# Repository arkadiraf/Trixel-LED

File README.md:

# Trixel-LED
Trixel LED is an interactive LED kit,
Create your own interactive Light elements by soldering basic shapes, such as triangle, square, pentagon and Hexagon. to create an interactive LED sculpture.

### [Trixel LED on Hackaday](https://hackaday.io/project/20510-trixel-led)

<br /><span xmlns:dct="http://purl.org/dc/terms/" property="dct:title">Trixel-LED</span> is licensed under a <a rel="license" href="http://creativecommons.org/licenses/by-nc-sa/4.0/">Creative Commons Attribution-NonCommercial-ShareAlike 4.0 International License</a>.

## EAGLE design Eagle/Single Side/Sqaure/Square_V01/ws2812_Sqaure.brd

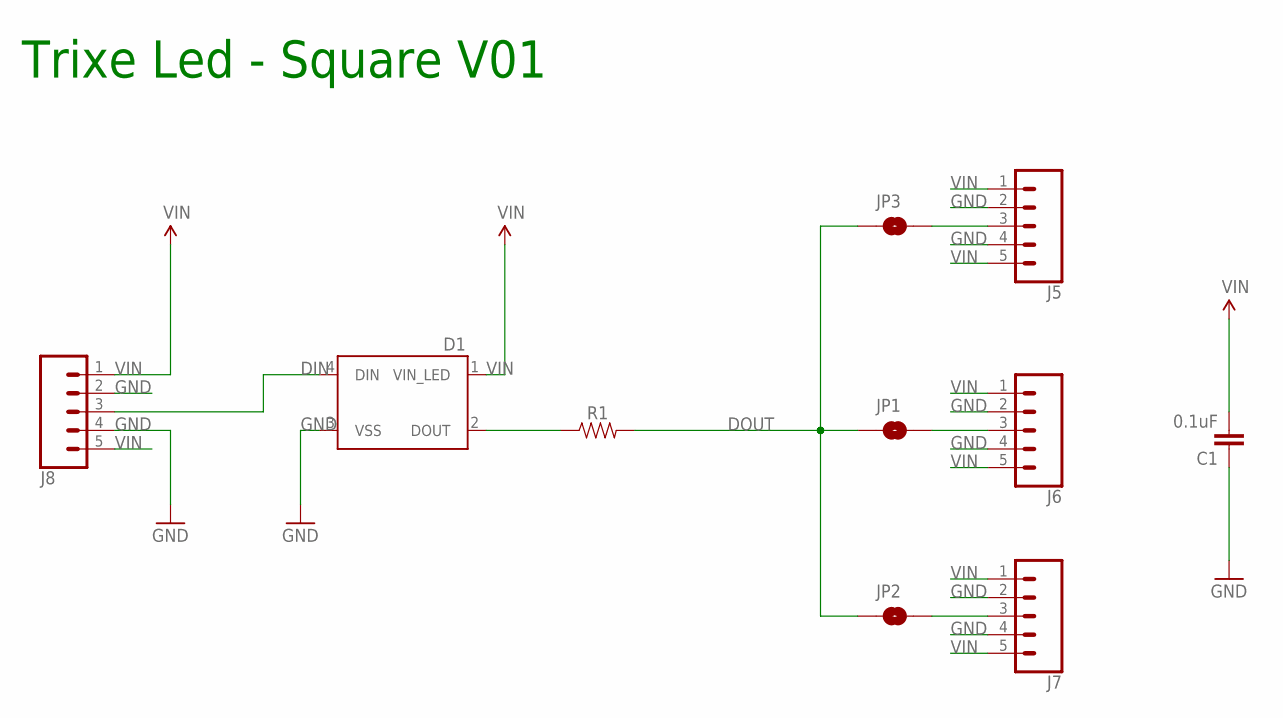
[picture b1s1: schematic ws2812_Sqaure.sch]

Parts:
C1: 0.1uF; 0805
D1: WS2812B
J5, J6, J7, J8: CONN_05PTH_LONGPADS; 1X05_LONGPADS
JP1, JP2, JP3: JUMPER-PAD-2-NOYES_SILK; PAD-JUMPER-2-NO_YES_SILK
R1: 0805

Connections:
DIN: D1.4 (DIN), J8.3
DOUT: JP1.1, JP2.1, JP3.1, R1.2
GND: C1.1, D1.3 (VSS), J5.2, J5.4, J6.2, J6.4, J7.2, J7.4, J8.2, J8.4
unnamed: J7.3, JP2.2
unnamed: J6.3, JP1.2
unnamed: J5.3, JP3.2
unnamed: D1.2 (DOUT), R1.1
VIN: C1.2, D1.1 (VIN_LED), J5.1, J5.5, J6.1, J6.5, J7.1, J7.5, J8.1, J8.5

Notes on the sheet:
Trixe Led - Square V01

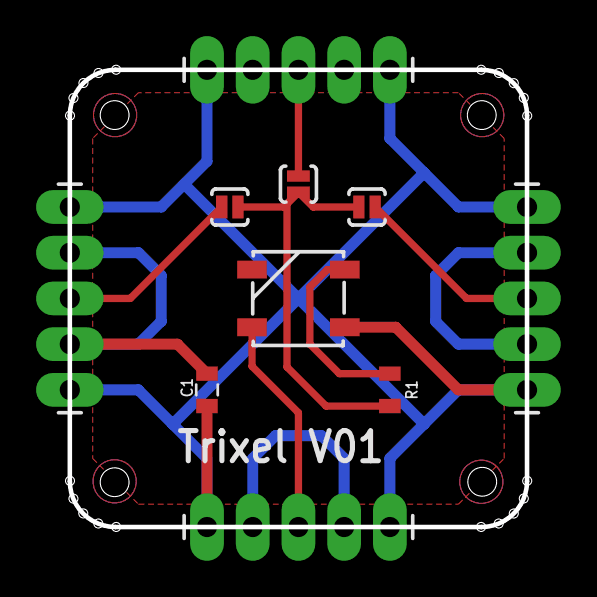
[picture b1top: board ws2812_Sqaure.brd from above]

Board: 2 copper layers, 25.4 x 25.4 mm, 10 parts (0 on the bottom side), 8 nets.

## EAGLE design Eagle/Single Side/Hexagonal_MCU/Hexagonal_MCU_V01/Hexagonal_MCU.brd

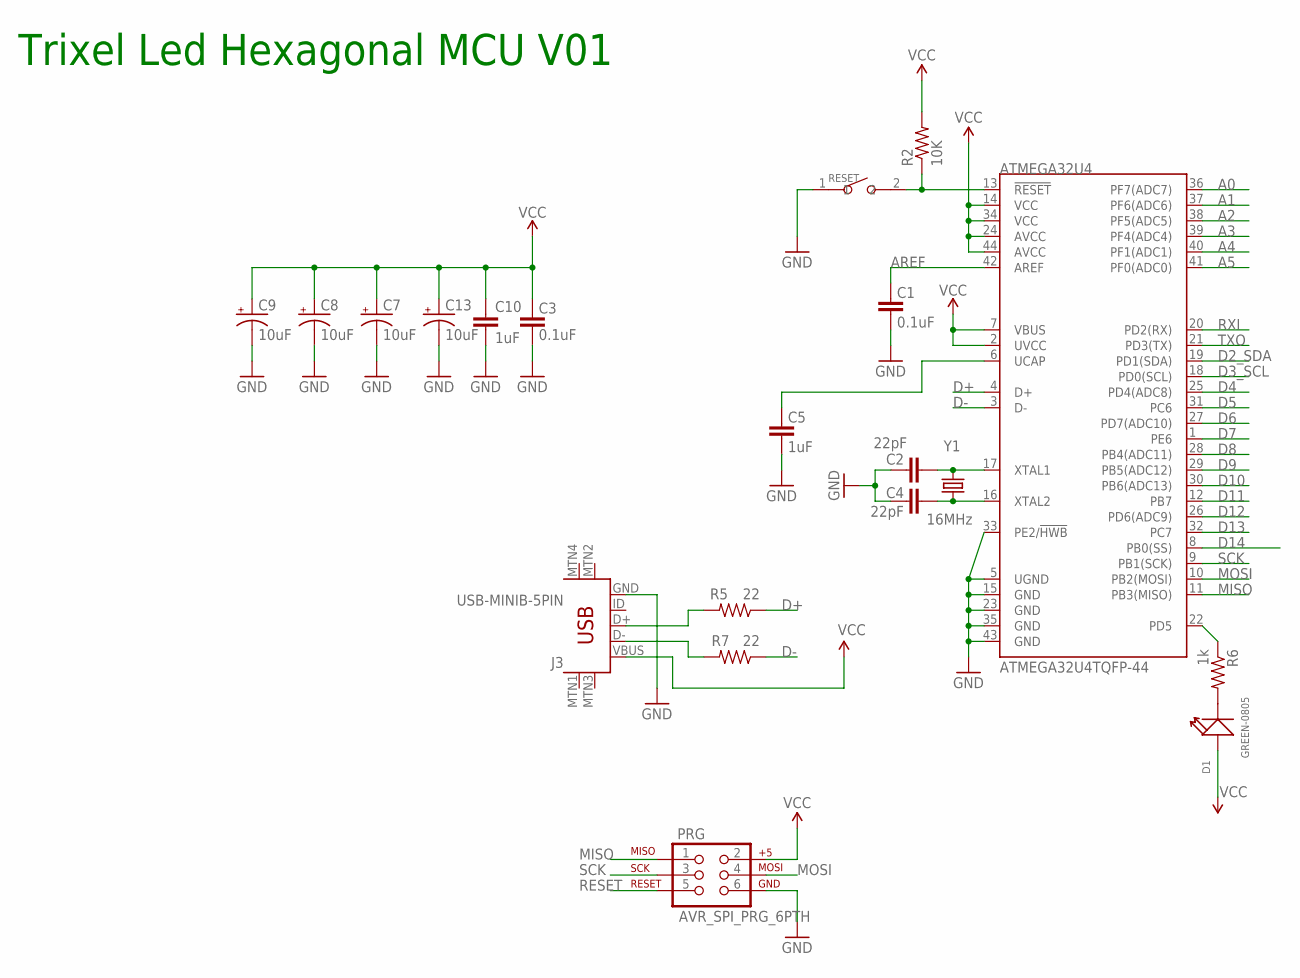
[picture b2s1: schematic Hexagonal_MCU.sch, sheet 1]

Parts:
ATMEGA32U4: ATMEGA32U4TQFP-44; TQFP44
C1, C3: 0.1uF; 0805
C2, C4: 22pF; 0805
C5, C10: 1uF; 0805
C7, C8, C9, C13: 10uF; EIA3216
D1: GREEN-0805; LED-0805
J3: USB-MINIB-5PIN; USB-MINIB
PRG: AVR_SPI_PRG_6PTH; 2X3
R2: 10K; 0805
R5, R7: 22; 0805
R6: 1k; 0805
RESET: B3U-1000P-2P-SMD; SW2-4.0X3.0X2.0
Y1: 16MHz; HC49US

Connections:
5V: ATMEGA32U4.2 (UVCC), ATMEGA32U4.7 (VBUS), ATMEGA32U4.14 (VCC), ATMEGA32U4.24 (AVCC), ATMEGA32U4.34 (VCC), ATMEGA32U4.44 (AVCC), C3.2, C7.A (+), C8.A (+), C9.A (+), C10.1, C13.A (+), D1.+, J3.VBUS, PRG.2, R2.2; also elsewhere on the board
A0: ATMEGA32U4.36 (PF7(ADC7))
A1: ATMEGA32U4.37 (PF6(ADC6))
A2: ATMEGA32U4.38 (PF5(ADC5))
A3: ATMEGA32U4.39 (PF4(ADC4))
A4: ATMEGA32U4.40 (PF1(ADC1))
A5: ATMEGA32U4.41 (PF0(ADC0))
AREF: ATMEGA32U4.42 (AREF), C1.2
D2_SDA: ATMEGA32U4.19 (PD1(SDA)); also elsewhere on the board
D3_SCL: ATMEGA32U4.18 (PD0(SCL))
D4: ATMEGA32U4.25 (PD4(ADC8))
D5: ATMEGA32U4.31 (PC6); also elsewhere on the board
D6: ATMEGA32U4.27 (PD7(ADC10))
D7: ATMEGA32U4.1 (PE6); also elsewhere on the board
D8: ATMEGA32U4.28 (PB4(ADC11)); also elsewhere on the board
D9: ATMEGA32U4.29 (PB5(ADC12))
D10: ATMEGA32U4.30 (PB6(ADC13))
D11: ATMEGA32U4.12 (PB7); also elsewhere on the board
D12: ATMEGA32U4.26 (PD6(ADC9))
D13: ATMEGA32U4.32 (PC7)
D14: ATMEGA32U4.8 (PB0(SS))
D+: ATMEGA32U4.4 (D+), R5.1
D-: ATMEGA32U4.3 (D-), R7.1
GND: ATMEGA32U4.5 (UGND), ATMEGA32U4.15 (GND), ATMEGA32U4.23 (GND), ATMEGA32U4.33 (PE2/!HWB), ATMEGA32U4.35 (GND), ATMEGA32U4.43 (GND), C1.1, C2.2, C3.1, C4.2, C5.1, C7.C (-), C8.C (-), C9.C (-), C10.2, C13.C (-), J3.GND, PRG.6, RESET.1; also elsewhere on the board
MISO: ATMEGA32U4.11 (PB3(MISO)), PRG.1
MOSI: ATMEGA32U4.10 (PB2(MOSI)), PRG.4
unnamed: ATMEGA32U4.16 (XTAL2), C4.1, Y1.1
unnamed: ATMEGA32U4.17 (XTAL1), C2.1, Y1.2
unnamed: J3.D-, R7.2
unnamed: D1.-, R6.2
unnamed: J3.D+, R5.2
RESET: ATMEGA32U4.13 (!RESET), PRG.5, R2.1, RESET.2
RXI: ATMEGA32U4.20 (PD2(RX))
SCK: ATMEGA32U4.9 (PB1(SCK)), PRG.3
TXLED: ATMEGA32U4.22 (PD5), R6.1
TXO: ATMEGA32U4.21 (PD3(TX))
UCAP: ATMEGA32U4.6 (UCAP), C5.2

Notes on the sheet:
Trixel Led Hexagonal MCU V01

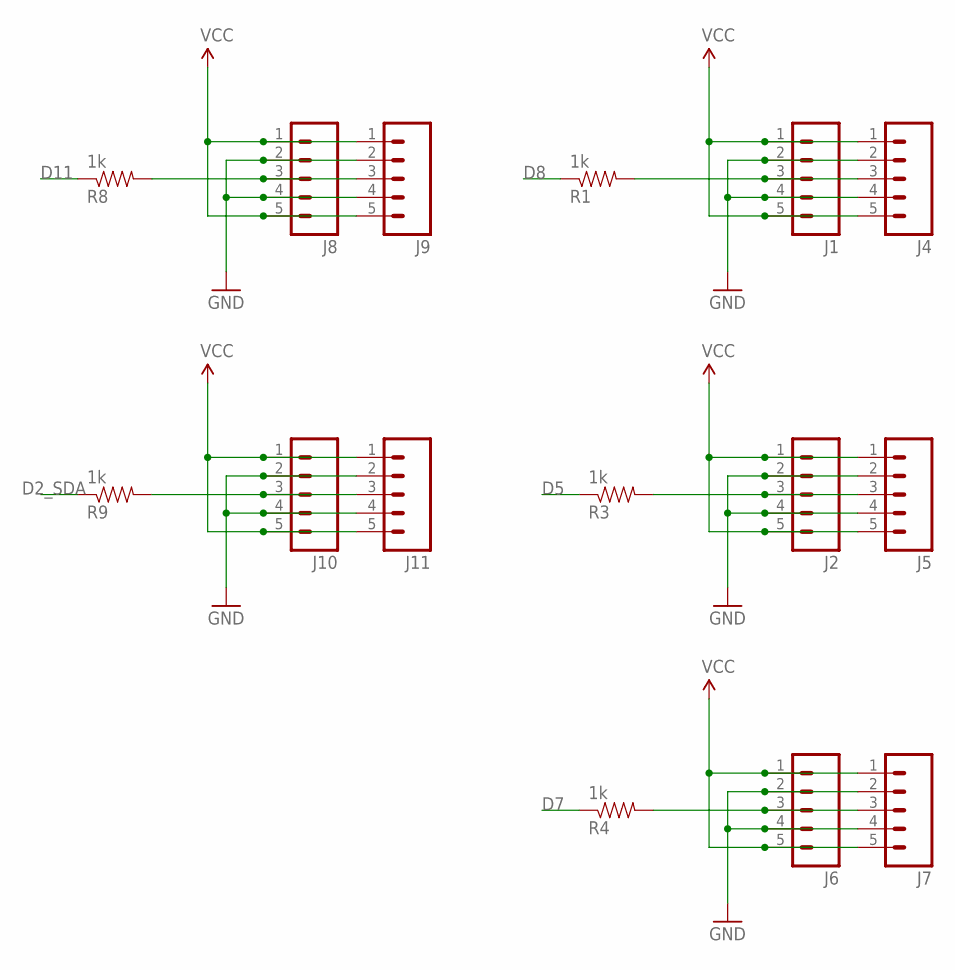
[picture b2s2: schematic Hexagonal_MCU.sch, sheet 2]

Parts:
J1, J2, J6, J8, J10: M05NO_SILK; 1X05_NO_SILK
J4, J5, J7, J9, J11: M05PTH_LONGPADS; 1X05_LONGPADS
R1, R3, R4, R8, R9: 1k; 0805

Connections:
5V: J1.1, J1.5, J2.1, J2.5, J4.1, J4.5, J5.1, J5.5, J6.1, J6.5, J7.1, J7.5, J8.1, J8.5, J9.1, J9.5, J10.1, J10.5, J11.1, J11.5; also elsewhere on the board
D2_SDA: R9.1; also elsewhere on the board
D5: R3.1; also elsewhere on the board
D7: R4.1; also elsewhere on the board
D8: R1.1; also elsewhere on the board
D11: R8.1; also elsewhere on the board
GND: J1.2, J1.4, J2.2, J2.4, J4.2, J4.4, J5.2, J5.4, J6.2, J6.4, J7.2, J7.4, J8.2, J8.4, J9.2, J9.4, J10.2, J10.4, J11.2, J11.4; also elsewhere on the board
unnamed: J2.3, J5.3, R3.2
unnamed: J1.3, J4.3, R1.2
unnamed: J6.3, J7.3, R4.2
unnamed: J8.3, J9.3, R8.2
unnamed: J10.3, J11.3, R9.2

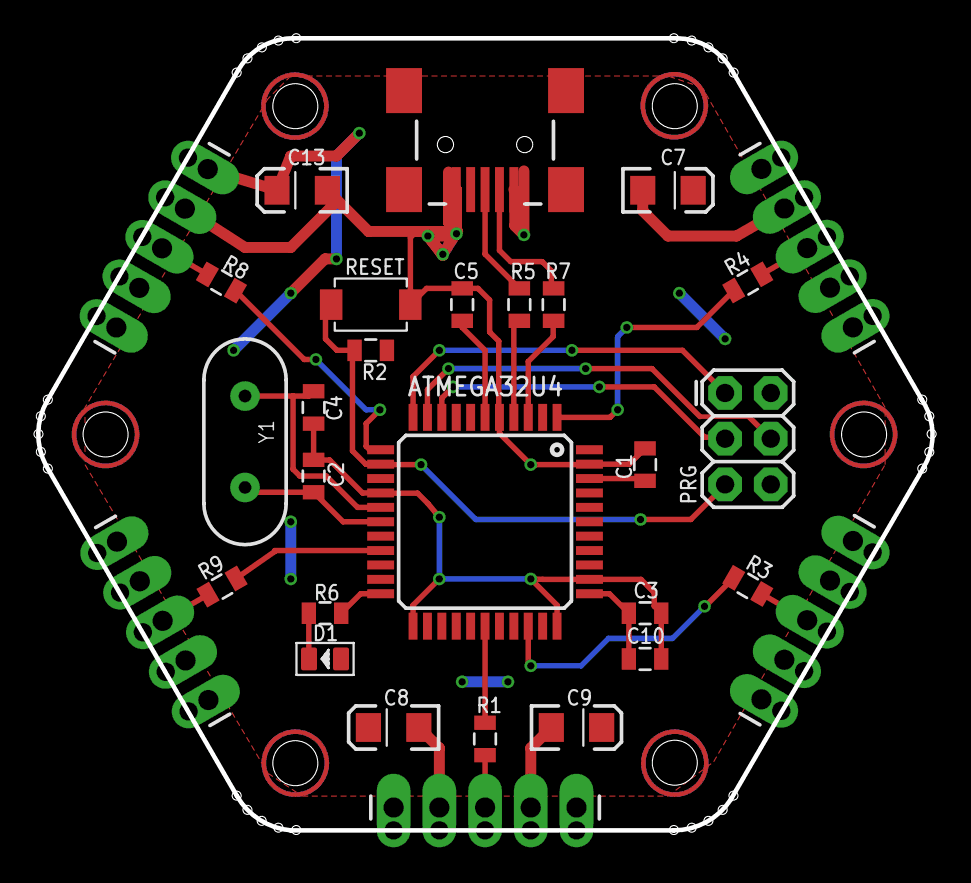
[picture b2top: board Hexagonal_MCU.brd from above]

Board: 2 copper layers, 49.7 x 44.0 mm, 35 parts (0 on the bottom side), 26 nets.

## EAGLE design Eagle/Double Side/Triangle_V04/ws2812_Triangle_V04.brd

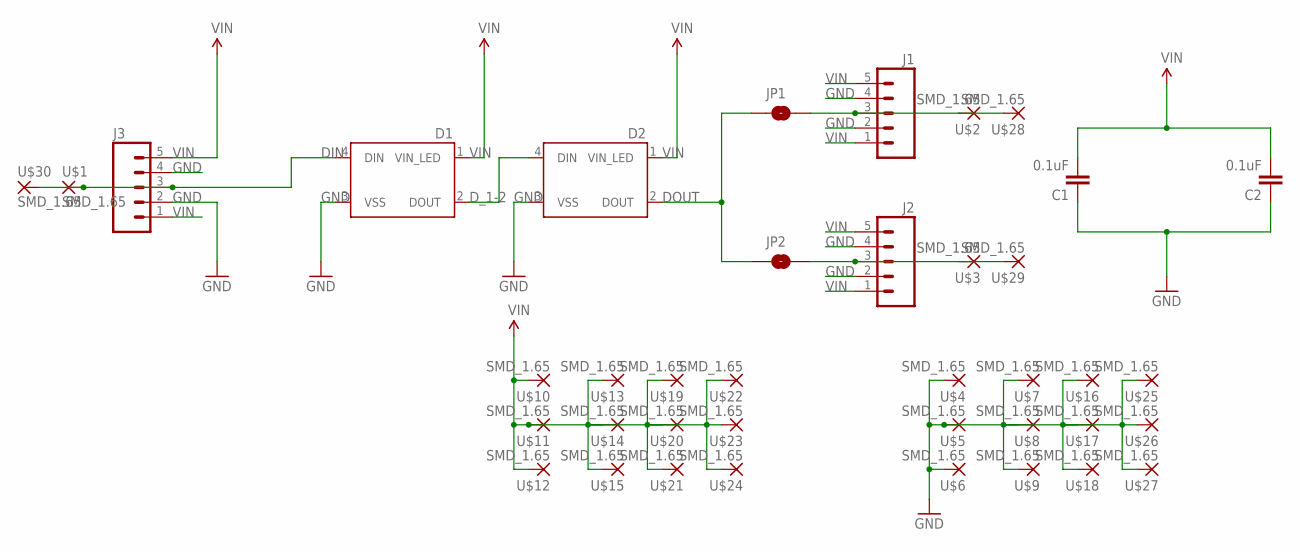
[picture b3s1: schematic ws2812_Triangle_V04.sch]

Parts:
C1, C2: 0.1uF; 0805
D1, D2: WS2812B
J1, J2, J3: M05NO_SILK; 1X05_NO_SILK
JP1, JP2: JUMPER-PAD-2-NOYES_SILK; PAD-JUMPER-2-NO_YES_SILK
U$1, U$2, U$3, U$4, U$5, U$6, U$7, U$8, U$9, U$10, U$11, U$12, U$13, U$14, U$15, U$16, U$17, U$18, U$19, U$20, U$21, U$22, U$23, U$24, U$25, U$26, U$27, U$28, U$29, U$30: SMD_1.65; SMD_PTH_1.65

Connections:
DIN: D1.4 (DIN), J3.3, U$1.P$1, U$30.P$1
DOUT: D2.2 (DOUT), JP1.1, JP2.1
D_1-2: D1.2 (DOUT), D2.4 (DIN)
GND: C1.1, C2.1, D1.3 (VSS), D2.3 (VSS), J1.2, J1.4, J2.2, J2.4, J3.2, J3.4, U$4.P$1, U$5.P$1, U$6.P$1, U$7.P$1, U$8.P$1, U$9.P$1, U$16.P$1, U$17.P$1, U$18.P$1, U$25.P$1, U$26.P$1, U$27.P$1
unnamed: J2.3, JP2.2, U$3.P$1, U$29.P$1
unnamed: J1.3, JP1.2, U$2.P$1, U$28.P$1
VIN: C1.2, C2.2, D1.1 (VIN_LED), D2.1 (VIN_LED), J1.1, J1.5, J2.1, J2.5, J3.1, J3.5, U$10.P$1, U$11.P$1, U$12.P$1, U$13.P$1, U$14.P$1, U$15.P$1, U$19.P$1, U$20.P$1, U$21.P$1, U$22.P$1, U$23.P$1, U$24.P$1

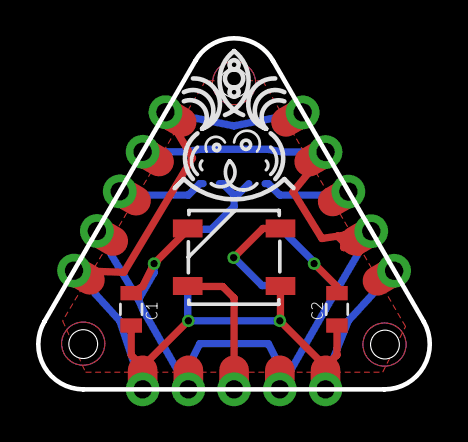
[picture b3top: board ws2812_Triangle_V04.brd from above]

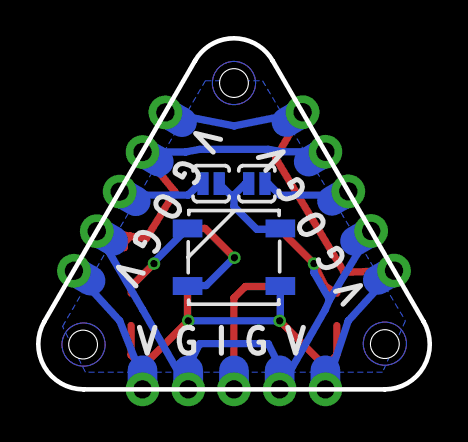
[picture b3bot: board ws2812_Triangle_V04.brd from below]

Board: 2 copper layers, 21.7 x 19.5 mm, 39 parts (18 on the bottom side), 7 nets.

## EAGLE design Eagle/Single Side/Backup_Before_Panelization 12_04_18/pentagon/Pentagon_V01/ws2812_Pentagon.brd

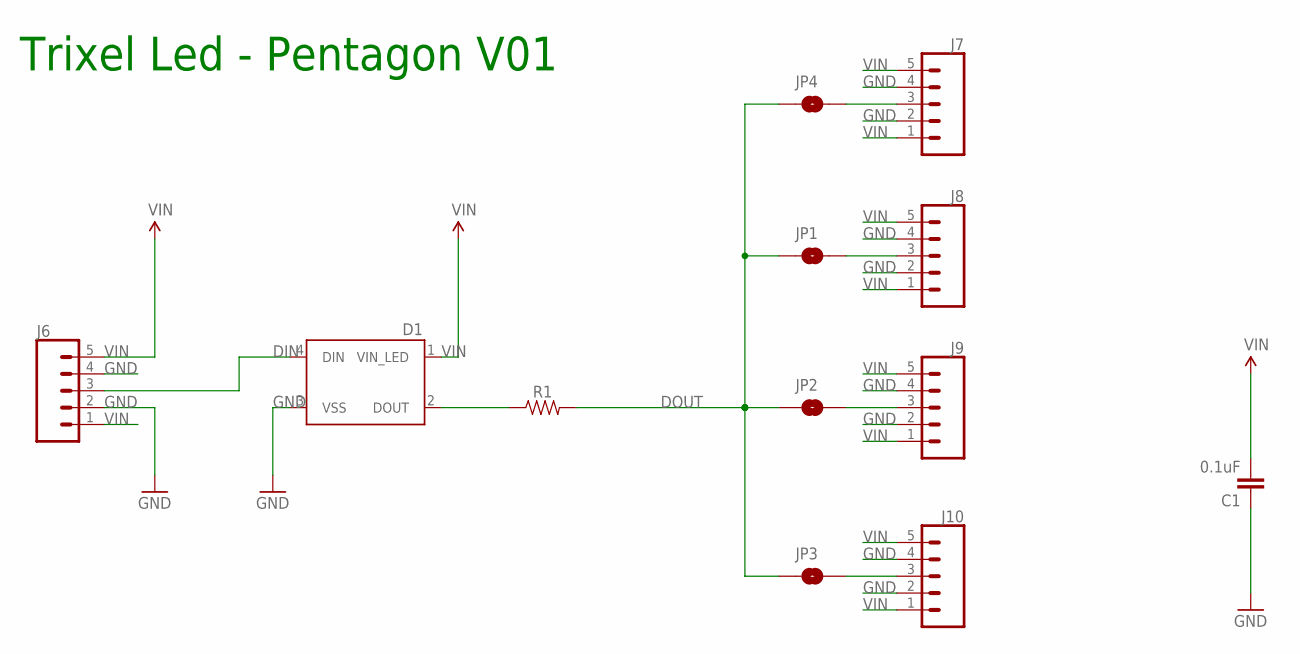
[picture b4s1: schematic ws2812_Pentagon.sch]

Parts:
C1: 0.1uF; 0805
D1: WS2812B
J6, J7, J8, J9, J10: CONN_05PTH_LONGPADS; 1X05_LONGPADS
JP1, JP2, JP3, JP4: JUMPER-PAD-2-NOYES_SILK; PAD-JUMPER-2-NO_YES_SILK
R1: 0805

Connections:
DIN: D1.4 (DIN), J6.3
DOUT: JP1.1, JP2.1, JP3.1, JP4.1, R1.2
GND: C1.1, D1.3 (VSS), J6.2, J6.4, J7.2, J7.4, J8.2, J8.4, J9.2, J9.4, J10.2, J10.4
unnamed: J9.3, JP2.2
unnamed: J8.3, JP1.2
unnamed: D1.2 (DOUT), R1.1
unnamed: J7.3, JP4.2
unnamed: J10.3, JP3.2
VIN: C1.2, D1.1 (VIN_LED), J6.1, J6.5, J7.1, J7.5, J8.1, J8.5, J9.1, J9.5, J10.1, J10.5

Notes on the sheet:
Trixel Led - Pentagon V01

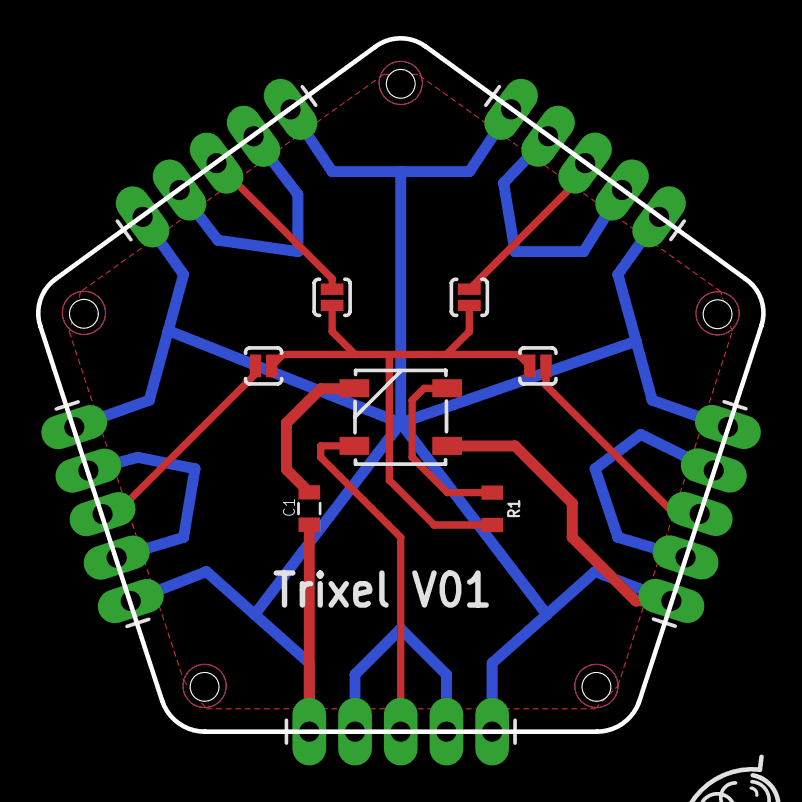
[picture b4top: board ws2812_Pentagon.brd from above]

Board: 2 copper layers, 40.3 x 38.5 mm, 12 parts (0 on the bottom side), 9 nets.

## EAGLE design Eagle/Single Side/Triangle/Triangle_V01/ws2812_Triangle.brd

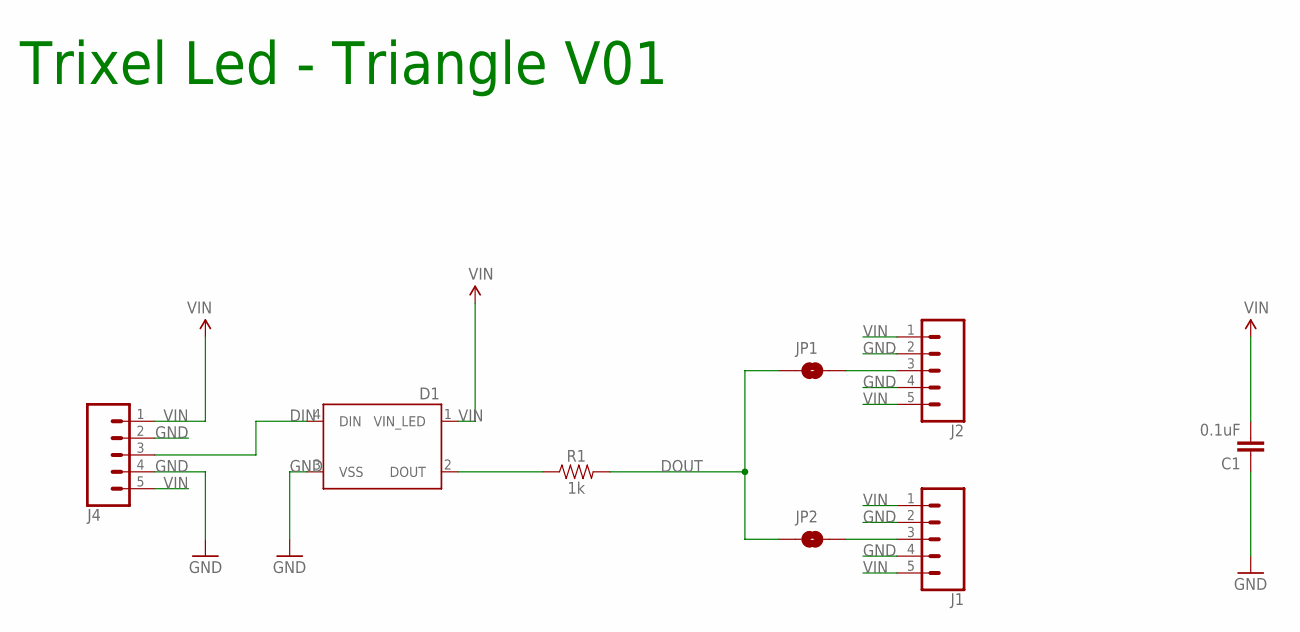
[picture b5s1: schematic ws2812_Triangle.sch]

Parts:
C1: 0.1uF; 0805
D1: WS2812B
J1, J2, J4: CONN_05PTH_LONGPADS; 1X05_LONGPADS
JP1, JP2: JUMPER-PAD-2-NOYES_SILK; PAD-JUMPER-2-NO_YES_SILK
R1: 1k; 0805

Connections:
DIN: D1.4 (DIN), J4.3
DOUT: JP1.1, JP2.1, R1.2
GND: C1.1, D1.3 (VSS), J1.2, J1.4, J2.2, J2.4, J4.2, J4.4
unnamed: J1.3, JP2.2
unnamed: J2.3, JP1.2
unnamed: D1.2 (DOUT), R1.1
VIN: C1.2, D1.1 (VIN_LED), J1.1, J1.5, J2.1, J2.5, J4.1, J4.5

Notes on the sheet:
Trixel Led - Triangle V01

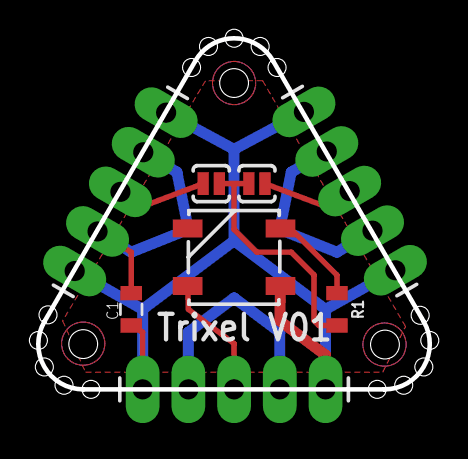
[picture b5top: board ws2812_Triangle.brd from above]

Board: 2 copper layers, 21.7 x 19.5 mm, 8 parts (0 on the bottom side), 7 nets.

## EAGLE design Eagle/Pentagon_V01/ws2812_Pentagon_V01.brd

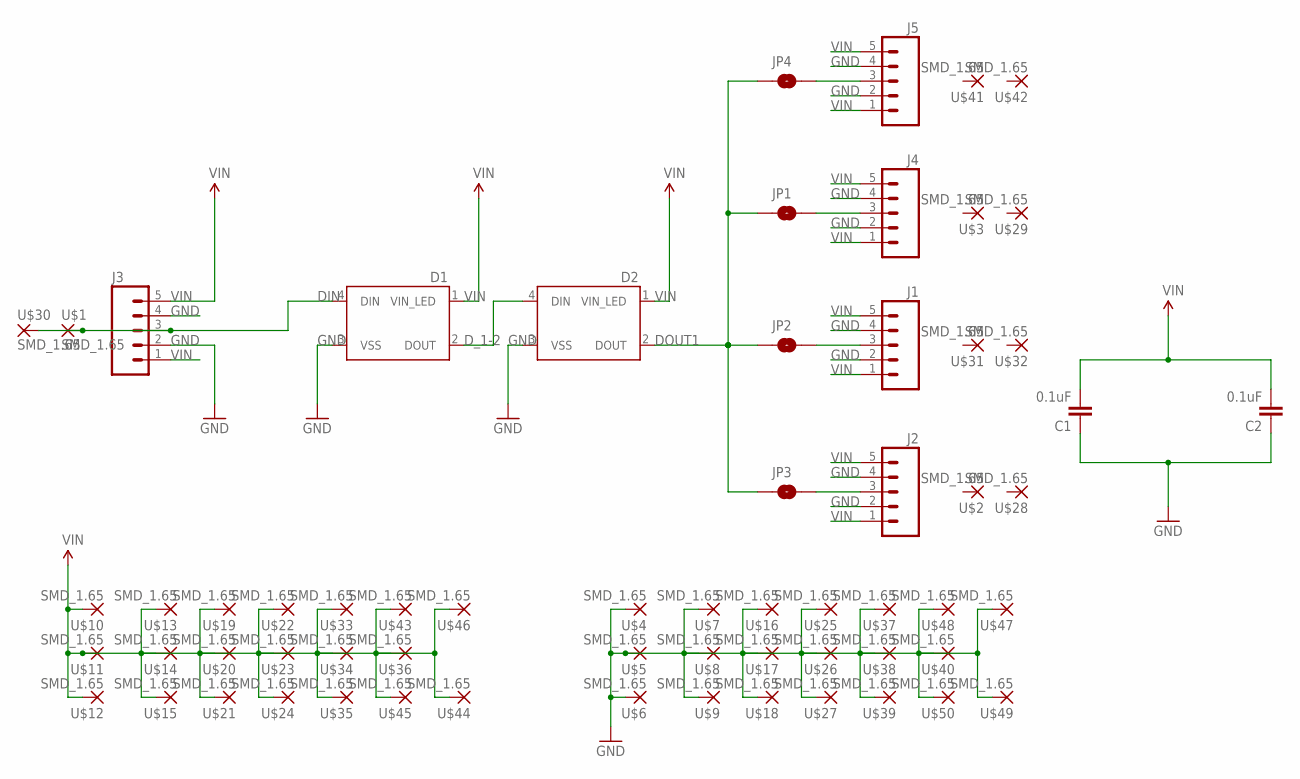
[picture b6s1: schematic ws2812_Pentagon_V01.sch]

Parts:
C1, C2: 0.1uF; 0805
D1, D2: WS2812B
J1, J2, J3, J4, J5: M05NO_SILK; 1X05_NO_SILK
JP1, JP2, JP3, JP4: JUMPER-PAD-2-NOYES_SILK; PAD-JUMPER-2-NO_YES_SILK
U$1, U$2, U$3, U$4, U$5, U$6, U$7, U$8, U$9, U$10, U$11, U$12, U$13, U$14, U$15, U$16, U$17, U$18, U$19, U$20, U$21, U$22, U$23, U$24, U$25, U$26, U$27, U$28, U$29, U$30, U$31, U$32, U$33, U$34, U$35, U$36, U$37, U$38, U$39, U$40, U$41, U$42, U$43, U$44, U$45, U$46, U$47, U$48, U$49, U$50: SMD_1.65; SMD_PTH_1.65

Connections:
DIN: D1.4 (DIN), J3.3, U$1.P$1, U$30.P$1
DOUT1: D2.2 (DOUT), JP1.1, JP2.1, JP3.1, JP4.1
D_1-2: D1.2 (DOUT), D2.4 (DIN)
GND: C1.1, C2.1, D1.3 (VSS), D2.3 (VSS), J1.2, J1.4, J2.2, J2.4, J3.2, J3.4, J4.2, J4.4, J5.2, J5.4, U$4.P$1, U$5.P$1, U$6.P$1, U$7.P$1, U$8.P$1, U$9.P$1, U$16.P$1, U$17.P$1, U$18.P$1, U$25.P$1, U$26.P$1, U$27.P$1, U$37.P$1, U$38.P$1, U$39.P$1, U$40.P$1, U$47.P$1, U$48.P$1, U$49.P$1, U$50.P$1
unnamed: J4.3, JP1.2
unnamed: J2.3, JP3.2
unnamed: J1.3, JP2.2
unnamed: J5.3, JP4.2
VIN: C1.2, C2.2, D1.1 (VIN_LED), D2.1 (VIN_LED), J1.1, J1.5, J2.1, J2.5, J3.1, J3.5, J4.1, J4.5, J5.1, J5.5, U$10.P$1, U$11.P$1, U$12.P$1, U$13.P$1, U$14.P$1, U$15.P$1, U$19.P$1, U$20.P$1, U$21.P$1, U$22.P$1, U$23.P$1, U$24.P$1, U$33.P$1, U$34.P$1, U$35.P$1, U$36.P$1, U$43.P$1, U$44.P$1, U$45.P$1, U$46.P$1

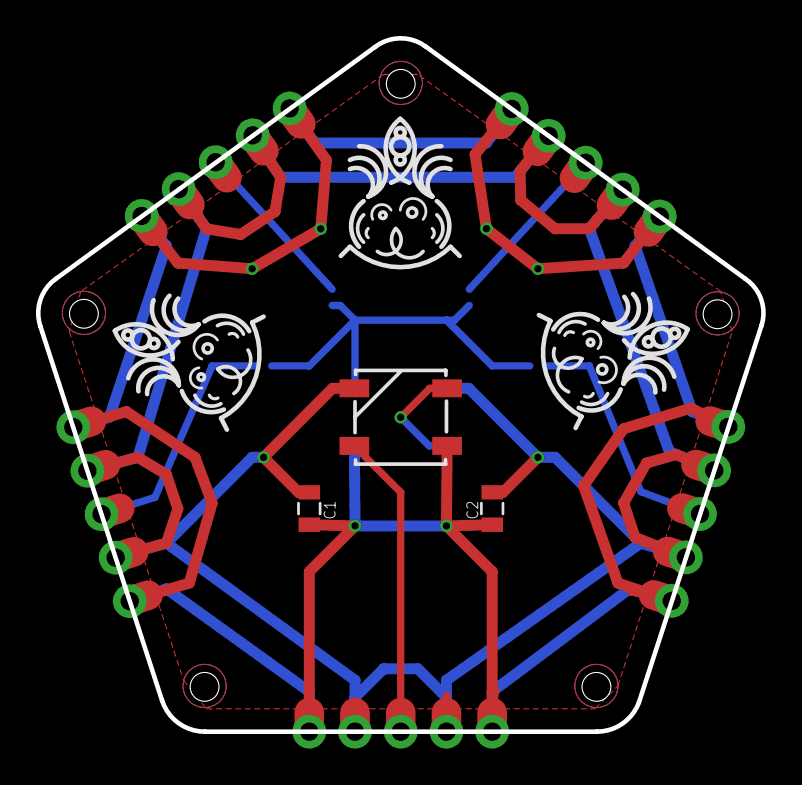
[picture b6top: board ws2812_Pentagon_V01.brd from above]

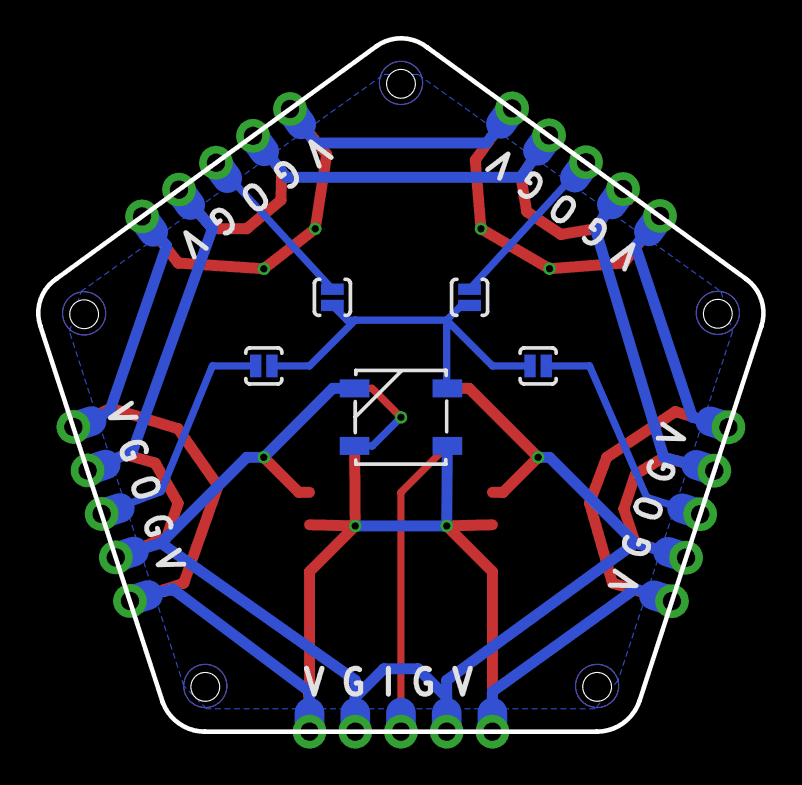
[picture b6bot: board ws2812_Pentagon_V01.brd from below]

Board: 2 copper layers, 40.3 x 38.5 mm, 63 parts (30 on the bottom side), 9 nets.

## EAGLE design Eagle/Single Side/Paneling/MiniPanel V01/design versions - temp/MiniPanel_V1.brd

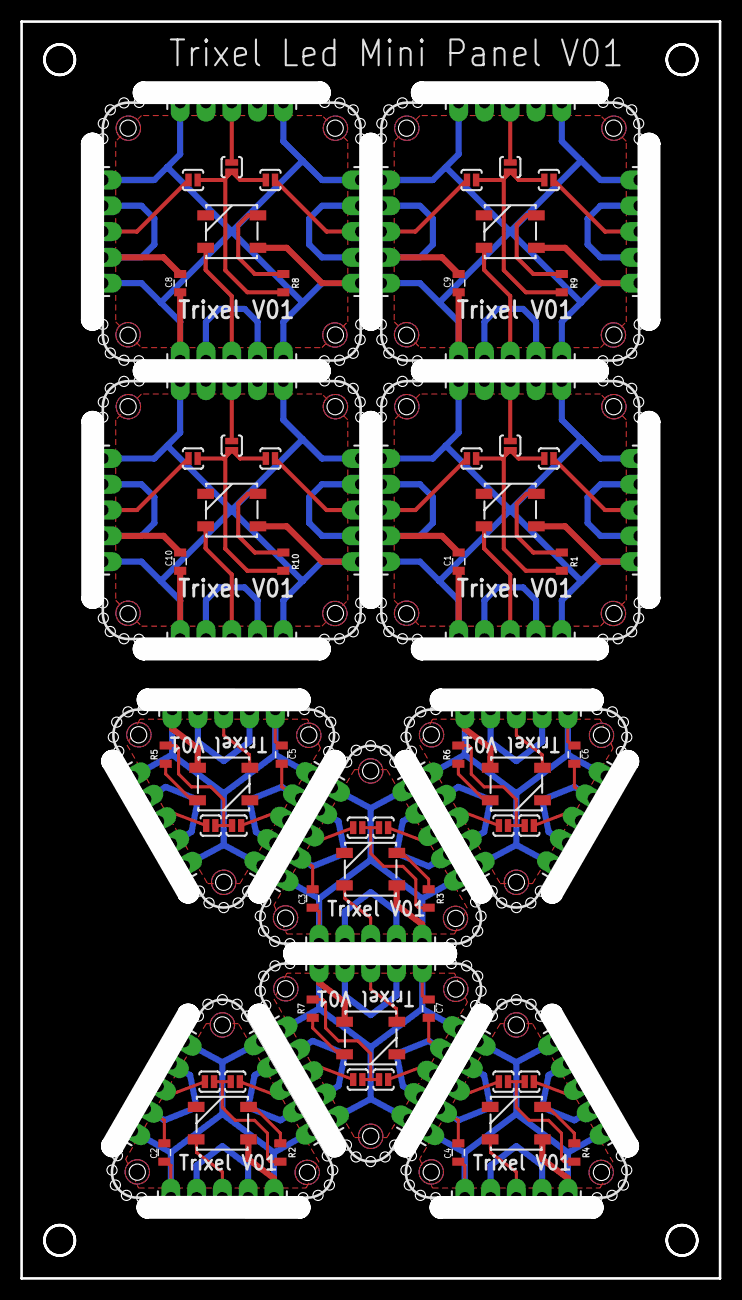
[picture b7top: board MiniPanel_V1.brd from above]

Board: 2 copper layers, 68.8 x 123.8 mm, 88 parts (0 on the bottom side), 74 nets.

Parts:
C1, C2, C3, C4, C5, C6, C7, C8, C9, C10: 0.1uF; 0805
D1, D2, D3, D4, D5, D6, D7, D8, D9, D10: WS2812B
J1, J2, J3, J4, J5, J6, J7, J8, J9, J10, J11, J12, J13, J14, J15, J16, J17, J18, J19, J20, J21, J22, J23, J24, J25, J26, J27, J28, J29, J30, J31, J32, J33, J34: 1X05_LONGPADS
JP1, JP2, JP3, JP4, JP5, JP6, JP7, JP8, JP9, JP10, JP11, JP12, JP13, JP14, JP15, JP16, JP17, JP18, JP19, JP20, JP21, JP22, JP23, JP24: JUMPER-PAD-2-NOYES_SILK; PAD-JUMPER-2-NO_YES_SILK
R1, R8, R9, R10: 0805
R2, R3, R4, R5, R6, R7: 1k; 0805

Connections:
DIN: D1.4, J22.3
DIN1: D2.4, J3.3
DIN2: D3.4, J7.3
DIN3: D4.4, J10.3
DIN4: D5.4, J13.3
DIN5: D6.4, J16.3
DIN6: D7.4, J19.3
DIN7: D8.4, J26.3
DIN8: D9.4, J30.3
DIN9: D10.4, J34.3
DOUT: JP1.1, JP2.1, JP15.1, R1.2
DOUT1: JP3.1, JP4.1, R2.2
DOUT2: JP5.1, JP6.1, R3.2
DOUT3: JP7.1, JP8.1, R4.2
DOUT4: JP9.1, JP10.1, R5.2
DOUT5: JP11.1, JP12.1, R6.2
DOUT6: JP13.1, JP14.1, R7.2
DOUT7: JP16.1, JP17.1, JP18.1, R8.2
DOUT8: JP19.1, JP20.1, JP21.1, R9.2
DOUT9: JP22.1, JP23.1, JP24.1, R10.2
GND: C1.1, D1.3, J1.2, J1.4, J2.2, J2.4, J4.2, J4.4, J22.2, J22.4
GND1: C2.1, D2.3, J3.2, J3.4, J5.2, J5.4, J6.2, J6.4
GND2: C3.1, D3.3, J7.2, J7.4, J8.2, J8.4, J9.2, J9.4
GND3: C4.1, D4.3, J10.2, J10.4, J11.2, J11.4, J12.2, J12.4
GND4: C5.1, D5.3, J13.2, J13.4, J14.2, J14.4, J15.2, J15.4
GND5: C6.1, D6.3, J16.2, J16.4, J17.2, J17.4, J18.2, J18.4
GND6: C7.1, D7.3, J19.2, J19.4, J20.2, J20.4, J21.2, J21.4
GND7: C8.1, D8.3, J23.2, J23.4, J24.2, J24.4, J25.2, J25.4, J26.2, J26.4
GND8: C9.1, D9.3, J27.2, J27.4, J28.2, J28.4, J29.2, J29.4, J30.2, J30.4
GND9: C10.1, D10.3, J31.2, J31.4, J32.2, J32.4, J33.2, J33.4, J34.2, J34.4
unnamed: J4.3, JP2.2
unnamed: J2.3, JP1.2
unnamed: J1.3, JP15.2
unnamed: J5.3, JP4.2
unnamed: D2.2, R2.1
unnamed: J6.3, JP3.2
unnamed: J8.3, JP6.2
unnamed: D3.2, R3.1
unnamed: J9.3, JP5.2
unnamed: J11.3, JP8.2
unnamed: D4.2, R4.1
unnamed: J12.3, JP7.2
unnamed: J14.3, JP10.2
unnamed: D5.2, R5.1
unnamed: J15.3, JP9.2
unnamed: J17.3, JP12.2
unnamed: D6.2, R6.1
unnamed: J18.3, JP11.2
unnamed: J20.3, JP14.2
unnamed: D7.2, R7.1
unnamed: J21.3, JP13.2
unnamed: D1.2, R1.1
unnamed: J25.3, JP17.2
unnamed: J24.3, JP16.2
unnamed: J23.3, JP18.2
unnamed: D8.2, R8.1
unnamed: J29.3, JP20.2
unnamed: J28.3, JP19.2
unnamed: J27.3, JP21.2
unnamed: D9.2, R9.1
unnamed: J33.3, JP23.2
unnamed: J32.3, JP22.2
unnamed: J31.3, JP24.2
unnamed: D10.2, R10.1
VIN: C1.2, D1.1, J1.1, J1.5, J2.1, J2.5, J4.1, J4.5, J22.1, J22.5
VIN1: C2.2, D2.1, J3.1, J3.5, J5.1, J5.5, J6.1, J6.5
VIN2: C3.2, D3.1, J7.1, J7.5, J8.1, J8.5, J9.1, J9.5
VIN3: C4.2, D4.1, J10.1, J10.5, J11.1, J11.5, J12.1, J12.5
VIN4: C5.2, D5.1, J13.1, J13.5, J14.1, J14.5, J15.1, J15.5
VIN5: C6.2, D6.1, J16.1, J16.5, J17.1, J17.5, J18.1, J18.5
VIN6: C7.2, D7.1, J19.1, J19.5, J20.1, J20.5, J21.1, J21.5
VIN7: C8.2, D8.1, J23.1, J23.5, J24.1, J24.5, J25.1, J25.5, J26.1, J26.5
VIN8: C9.2, D9.1, J27.1, J27.5, J28.1, J28.5, J29.1, J29.5, J30.1, J30.5
VIN9: C10.2, D10.1, J31.1, J31.5, J32.1, J32.5, J33.1, J33.5, J34.1, J34.5

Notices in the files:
parts and their libraries:
SparkFun-Capacitors: Licensing: Creative Commons ShareAlike 4.0 International - https://creativecommons.org/licenses/by-sa/4.0
